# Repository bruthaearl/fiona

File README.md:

# fiona
things related to fiona's project.

more documentation to follow.

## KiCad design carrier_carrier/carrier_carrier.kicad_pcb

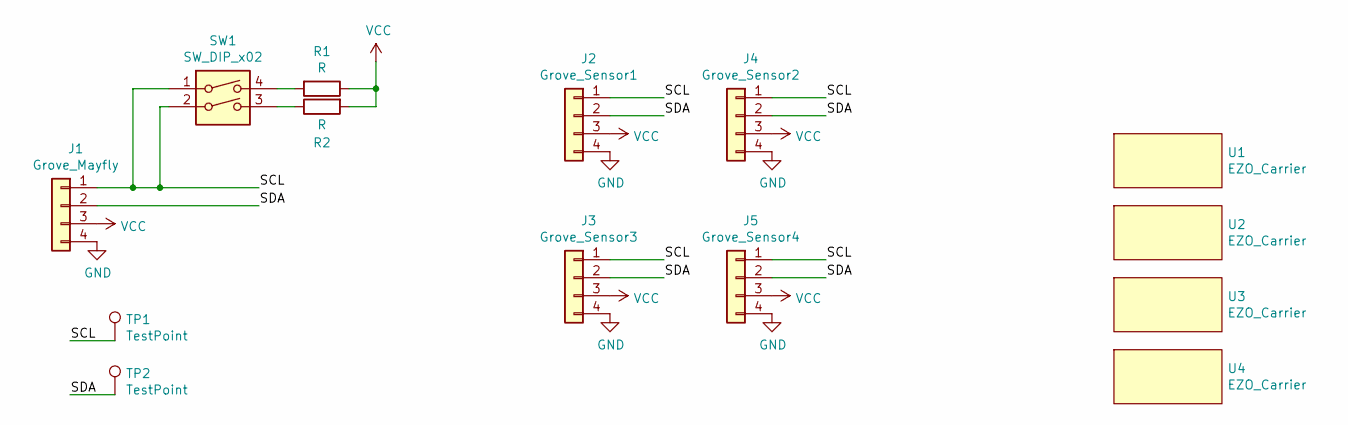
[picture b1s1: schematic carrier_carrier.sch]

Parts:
J1: Grove_Mayfly; Grove
J2: Grove_Sensor1; Grove
J3: Grove_Sensor3; Grove
J4: Grove_Sensor2; Grove
J5: Grove_Sensor4; Grove
R1, R2: R; R_Axial_DIN0204_L3.6mm_D1.6mm_P5.08mm_Horizontal
SW1: SW_DIP_x02; SW_DIP_SPSTx02_Slide_6.7x6.64mm_W7.62mm_P2.54mm_LowProfile
TP1, TP2: TestPoint; TestPoint_THTPad_2.0x2.0mm_Drill1.0mm
U1, U2, U3, U4: EZO_Carrier

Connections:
/SCL: J1.1, J2.1, J3.1, J4.1, J5.1, SW1.1, SW1.2, TP1.1
/SDA: J1.2, J2.2, J3.2, J4.2, J5.2, TP2.1
GND: J1.4, J2.4, J3.4, J4.4, J5.4
unnamed: R1.2, SW1.4
unnamed: R2.1, SW1.3
VCC: J1.3, J2.3, J3.3, J4.3, J5.3, R1.1, R2.2

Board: 2 copper layers, 14 parts (0 on the bottom side), 6 nets, no tracks yet.

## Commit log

2021-05-19 ezo_uart_lib_test initial commit
2021-05-19 folder cleanup
2021-06-05 pcb update
2022-02-11 big commit
2022-02-11 repo cleanup
2022-06-03 uuid header
2022-06-03 test comment
